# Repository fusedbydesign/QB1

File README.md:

# QB1

QB1 is a rapid prototyping system for ESP32 devices. The system was designed for ESPHome sensors, but it could potentially be used for other applications.

## Features

* Rapid prototyping for testing sensors and automation in the intended environment.
* Modular design allows each device to be built with the appropriate sensors, power interface, and mounting solutions. The five cube faces can each be used for a different purpose. 
* The QB1 specification allows multiple sensors to exist on the same device without conflict.
* Easy to make. 
  * The enclosure can be produced using a low cost 3D printer. 
  * The main board can be assembled quickly with basic soldering skills.
  * Many common sensor can be integrated by printing a custom face plate and connecting the sensor to the main board with Dupont wire. 
* Once constructed, the device can be modified without soldering, enabling rapid modification of devices. 

## Example Projects

<table>
  <tr>
    <td>
      <br>
      Washing machine monitor using SW-420 vibration sensor to detect when the machine is running and V53L0X distance sensor to tell when lid has been opened. The device is mounted to the washing machine using a custom mounting plate and velcro tape, and it is used to send a notification when wet clothes have been left in the wachine machine. 
    </td>
    <td>
      <br>
      Plug-in temperature and humidity monitor using SHT40. The device plugs in to the wall using an off-the-shelf USB wall plug that is inside the QB1 enclosure and held in place using a custom face plate. 
    </td>
  </tr>

  <tr>
    <td>
      <br>
      A wall-mounted human presence sensor that combines an AM312 PIR motion sensor and a wired magnetic reed door sensor. The device is used turn on/off lights in the area based on human presence. 
    </td>
    <td>
      <br>
      A ceiling-mounted device that combines human presence detection using an AM312 PIR motion sensor, car presence detection using an HC-SR04 distance sensor, and garage door control/status using a <a href="https://github.com/PaulWieland/ratgdo">ratgdo-compatible</a> peripheral board. 
    </td>
  </tr>
</table>

## Building

The core QB1 components can be built with basic tools and skills. 

> [!WARNING]
> This is an open source project and a constant work in progress, not a finished product. Production files and PCBWay projects are provided only for convenience. Boards ordered using these files/projects may have flaws due to issues in the design or assembly. The maintainers of this project are not responsible for loss or damages due to these flaws. Please submit any issues you find using the issue tracker for this project.  

### Tools Required

* A [soldering iron](https://amzn.to/4105tMp) and related supplies. The QB1 main board contains only through hole components, so only basic soldering skills are required. Some peripheral boards require surface mount components and more advanced soldering skills. 
* A basic 3D printer to print the QB1 enclosure and face plates. Using a print-on-demand service (or a friend with a printer) can help get you started, but having your own printer makes it much easier to print new faceplates to modify the device in the future. The [Bambu Lab A1 Mini](https://bambulab.com/en/a1-mini) (without AMS) is inexpensive and well-suited to printing smaller items like the QB1 enclosure. 
* A small Phillips screwdriver (or driver matching the head of the screws, if not Phillips). The shaft must be smaller than 5.5 mm in diameter in order to fit in the holes in the bottom of the enclosure. 
* A small tube of super glue to build some of the enclosure parts. 
* (Optional) A [hot glue gun](https://amzn.to/40Knkqm). Many sensors that operate at 3.3v can be connected directly to the main board using Dupont wire. It's best to glue these connectors in place so they don't fall off in operation. The hot glue can easily be removed later. 

### Components Required

All components other than custom circuit boards and 3D-printed enclosure parts can be purchased in small quantities from Amazon or AliExpress.

* A QB1 main board. You can order a small batch of 5 main boards using this [PCBWay project](https://www.pcbway.com/project/shareproject/QB1_Main_Board_for_ESP32_Development_Kit_a3892956.html). You can also use the zipped Gerber files provided in a QB1 release to order the board from another supplier. 
* A [30-pin ESP32 development board](https://amzn.to/4lGmVin) with USB-C connector. You can choose a device with the right storage and other features for your application.
* (7) [Female 15-pin, single row board header with 2.54 mm pin spacing](https://amzn.to/4suHbWA). You will need two for the ESP32 dev kit socket and up to 5 for the remaining QB4 faces.
* [Screws](https://amzn.to/47RIYwE): M3, self-tapping, coarse threaded with pan/button head. The head must be between 3.5mm and 5.5mm in diameter.
  * (8) To secure the main board and close the case, use screws that are 8mm long (not counting the head), but screws up to 16 mm in length will also work.
  * (4, Optional) To make the top plate removable and functional, use screws that are exactly 8mm long (not counting the head). In most cases, the top plate is not used for sensors or other peripherals, because the four side plates are sufficient. In this case, it can be glued in place, and these screws are unnecessary.
* [Printed enclosure parts](https://makerworld.com/en/collections/23142249-qb1): A top, a bottom, face plates for mounting and peripherals, and blank plates to cover any remaining faces. 
* (Optional) Any additional components required for peripherals. See peripheral doc for mor information. Some generally useful items to have on hand are:
  * [Dupont wire](https://amzn.to/4slY8CT) with male connector on one end and female connector on the other. The wire should be between 10 and 20cm in length. This wire is useful for hooking up small sensors that do not require a QB1 peripheral board. 
  * [Small prototyping boards](https://amzn.to/4sSRvYk) (e.g 40 mm by 60 mm) can be used to develop peripheral boards.  

### Assembling the Boards

Follow the instructions provided to assemble the QB1 [main board](/mainboards/ESP32DK) and any peripheral boards.

### Assembling the QB1

* Insert the ESP32 development board into the pair of 15-pin sockets on the bottom of the QB1 main board. Use the labels on the PCB silk screen to orient the ESP32 board correctly.  
* Place the main board on the tall screw hole supports inside the enclosure bottom. Ensure that the board is oriented correctly so that the ESP32 dev board screw holes rest on the lower supports and the USB-C connector faces the opening on the bottom plate. Screw the main board in place with 4 M3 screws.
* Place the USB-C port cover in the enclosure bottom and glue it in place with super glue. 
* Attach peripherals
  * For peripherals that are attached by wires, plug the connector into the appropriate place in the main board. Secure the connectors in place using hot glue, and attach the peripheral to its custom face plate.  
  * Attach peripheral boards to their custom plates. These boards typically have male header that connects to the main board and is held in place by the enclosure. This connection will be made when the face plates are inserted in a later step.
* Place the QB1 enclosure top upside down on a flat surface.
* Insert a face plate into the QB1 top face. The plate will be held lightly in place by friction against the screw supports. To hold this plate more firmly, place two top plate holders over the plate and screw them in place. 
* Place face plates into the four slots at the top of the enclosure. 
* Place the QB1 enclosure bottom upside down onto the top. To ensure that the peripheral boards are attached correctly to the main board connector: lift each perhipheral board slightly to make the connection, then lower the enclosure bottom after all connections are made. It may be necessary to wiggle the legs of the enclosure top to ensure that they are seated correctly. 
* Screw the bottom to the top using 4 M3 screws. 

## FAQ

* **When would I use this?** QB1 is useful in a few circumstances: 
  * When you want to quickly prototype a device to test its behavior in the intended environment. 
  * When you need multiple sensors in a single device.
  * When you need to deploy sensors in a basement/garage or other utility area where appearance/size is less important.
* **When wouldn't I use this?** There are some limitations:
  * QB1 is nearly 80 mm long on each side. For many applications, a custom board and enclosure would be smaller. 
* **How do I use this for home sensing and automation?** See the [ESPHome site](https://esphome.io) for more information. A typical solution is to set up a [Home Assistant](https://www.home-assistant.io) hub that takes information from QB1 devices (and other sensors). 
* **Does the QB1 look good?** Looks are subjective, but yes. 
* **What sensors are supported?** Any sensor that operates at 3.3v and has a fairly simple interface (a few IO pins, I2C, SPI, etc.) can be wired directly to the appropriate pins on the QB1 main board. Then all that is needed is a face plate that holds the sensor in place. Sensors/components with more complicated interfaces can be integrated by developing a peripheral board with additional interface components. 
* **How do I add an external connector?** The best ways to achieve this are:
  * Locate a panel-mount connector and attach it to the main board using wires.
  * Make a simple peripheral board with connectors soldered to it. A male JST-XH connector soldered to a peripheral board will sit approximately flush with the face plate. 
* **How do I configure ESPHome?** Locate ESPHome documentation for the sensor you would like to configure. Look at the main board documentation or silk screen markings on the main board to determine which pins are attached to each connector position. 
* **What happens if I plug in multiple peripherals? How do I keep them from conflicting?** The QB1 spec assigns pins to each peripheral position. Some pins are shared, such as pins intended for the I2C and SPI buses. Each peripheral position also has four pins that are dedicated to that position (with the exception of EB2 and EB5, that have the same set of "dedicated" pins). Where possible, a peripheral should use dedicated pins or buses in order to avoid conflict.
* **The screws are too tight/loose. What is wrong?** To keep the part count low, the design does not use screw inserts, and instead uses self-tapping screws that screw into 3D-printed holes. Due to variation in printers and settings, these holes may be slightly too large/small. To fix it:
  * If the hole is too tight, carefully drill it out. Forcing the screw in without drilling may cause the plastic to crack.
  * If the hole is too loose, add a small amount of hot glue, allow the glue to cool, then screw in the screw. Hot glue can also be used to repair screw holes that are cracked or worn out. 
* **What options should I select when ordering boards from PCBWay?** Unless you have a compelling reason to change the options, you can use the default settings when ordering boards. 
* **How can I get a QB4 if I don't have a 3D printer or soldering iron?** There are a few options:
  * Order assembled boards and printed enclosure parts from an electronics fab and print-on-demand service, respectively.
  * Join a local maker space that has 3D printers and electronics assembly tools. 
  * Find someone near you with a 3D printer and buy enclosure parts from them. Many people who own a 3D printer would be thrilled to print something for you in exchange for a small amount of money to pay for their filament habit. 
  * Use this project as an excuse to buy what you need. Soldering supplies are inexpensive. Small/basic 3D printers are now cheap and reliable enough that they should be considered essential tools for any homeowner. 

## Support and Transparency

If you are fortunate enough to have a store near you that sells basic electronics components, please consider buying components from them instead of using the links on this site or ordering from internet retailers.

I (the developer of QB1) earn a commission from tools and components purchased though links on this site. As an Amazon Associate, I earn from qualifying purchases. I also earn a commission from circuit boards ordered from PCBWay. I chose the recommended tools/components by searching for products with the correct specs and features, but I haven't tried them all. Please review the product description, specs, reviews, etc. before ordering.

If you would like to directly support the development of QB1, you can donate using [Buy me a coffee](https://buymeacoffee.com/fusedbydesign).

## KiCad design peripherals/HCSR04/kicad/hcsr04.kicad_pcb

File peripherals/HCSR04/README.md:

# HC-SR04 Distance Sensor Peripheral Board for QB1

The HC-SR04 is a low-cost ultrasonic distance sensor with sub-centimeter precision and a maximum range of 4 meters. Unfortunately, it needs to operate at 5V for best performance, and its output must be converted to 3.3V in order to interface with the ESP32 without damaging it. This board provides a safe, reliable 5v/3.3V interface between the ESP32 and an HC-SR04. The board also provides a physical mounting surface for the HC-SR04, and a second level converter that can be used to connect another HC-SR04 that is mounted elsewhere. 

> [!TIP]
> There are other distance sensors that can interface more easily with the QB1 without level conversion. There are also HC-SR04P modules that can be powered using 3.3v, but the maximum range will be slightly reduced. Be prepared to test multiple distance sensors to find the ones that work best for your application.

## Printed Circuit Board

The easiest way to get the PCB is to order a batch using this [PCBWay project](https://www.pcbway.com/project/shareproject/QB1_peripheral_board_for_HC_SR04_distance_sensor_22c7cf84.html). Due to the options for mounting the sensor module, and the unusual way the module is mounted in some options, DIY assembly is highly recommended. Assembly only requires a few through hole components and some basic soldering skills. 

## Required components

| Count | Description |
|---|---|
| 1 | [HC-SR04 module](https://amzn.to/4rNMYFK)|
| 1 | 15 pin male header, 2.54mm pin spacing, angled |
| 2 | 100k Ohm resistor, through hole, axial |
| 2 | 51k Ohm resistor, through hole, axial |
| 4 | Single pin male header, straight |
| 1 | (Optional) 4-pin male header, 2.54mm spacing, angled | 

Component notes:
* For the angled header, you can use commonly-available [breakaway header](https://amzn.to/4sulC8Q) and break it to the correct size. Ensure the header has a short post (the straight part---approximately 3mm long) and a longer tail (the bent part---approximately 6mm long after the bend). The post of the header is soldered to the board and the connector sits 4-5mm off the board. These dimensions ensure a proper fit using the face plate for this connector. Other connectors may be used by modifying the face plate.
* Any [resistors](https://amzn.to/4bEVNeX) with 5% or smaller tolerance and at least 1/4 watt power capacity will work. You can modify the resistance to match the resistor values you have available, as long as the ratio remains approximately 1:2. For example, a 47k Ohm reistor can be used instead of 51k. Increasing the resistance (while maintaining a ratio of 1:2) is not recommended, but the values can be lowered to a minimum of 1k/2k, if desired. The value of 51k/100k was chosen to give acceptable performance in most environments while minimizing power draw. If the sensor will be used in an environment with a large amount of electromagnetic interference, then lower resistance values may give more reliable performance, at the expense of slightly more power draw.

## Assembly

The board supports two different orientations for the HC-SR04:
* Straight mount so that the HC-SR04 and board occupy a single cube face. This is the most common orientation.
* Edge mount so the board can be mounted in one of the side faces and the HC-SR04 points in the direction of the top face. This orientation allows the HC-SR04 to point in the direction of the top face, without the complications associated with mounting the board on the top face. 

Take note of the order in which the components must be placed and soldered---the HC-SR04 covers some of the other components, so it must be placed last. To assemble:

1. Place and solder the resistors as shown in the silk screen on the back of the board, and the 15-pin header on the front of the board.  
1. If the second interface will be used to connect a second HC-SR04 to the QB1, place and solder the 4-pin angled header.
1. Attach the HC-SR04 module and related components
  * For straight mount, start by placing and soldering the single pin headers on the front side of the board, as shown in the silk screen. These headers are not connected, and are only used for structural support. Next, bend the pins on the HC-SR04 module to make them straight, then place the HC-SR04 module, ensuring the pins on the single headers extend through the mounting holes at the corners of the module. With the module seated flush against the base of the headers, solder the module pins to the board. Finally, cut the excess pin length from the module pins and single pin headers using wire cutters. 
  * For edge mount, place and solder the HC-SR04 module in the U2 position on the back of the board, with the sensor pointing away from the board. Cut the excess pin length from the HC-SR04 connector.
  
The peripheral board mounts to the main board in the inside position, in order to accommodate the depth of the sensor module. 

## Enclosure 

Print or otherwise obtain the [face plate](https://makerworld.com/en/models/2567128-qb1-face-plate-for-hc-sr04-peripheral-board) to incorporate this peripheral board into a QB1. To complete the enclosure, you will also need other pieces from [this collection](https://makerworld.com/en/collections/23142249-qb1).

## Operation

For the HC-SR04 mounted to the peripheral board, the trigger pin is connected to TRIG1, and and the echo pin is connected to ECHO1. For the optional external HC-SR04, these signals are TRIG2 and ECHO2. See the silk screen on the board for the connection between these signals and QB1 peripheral pins. 

See the [ESPHome](https://esphome.io/components/sensor/ultrasonic/) page on ultrasonic distance sensors for more information about the HC-SR04 and how to use it with ESPHome.

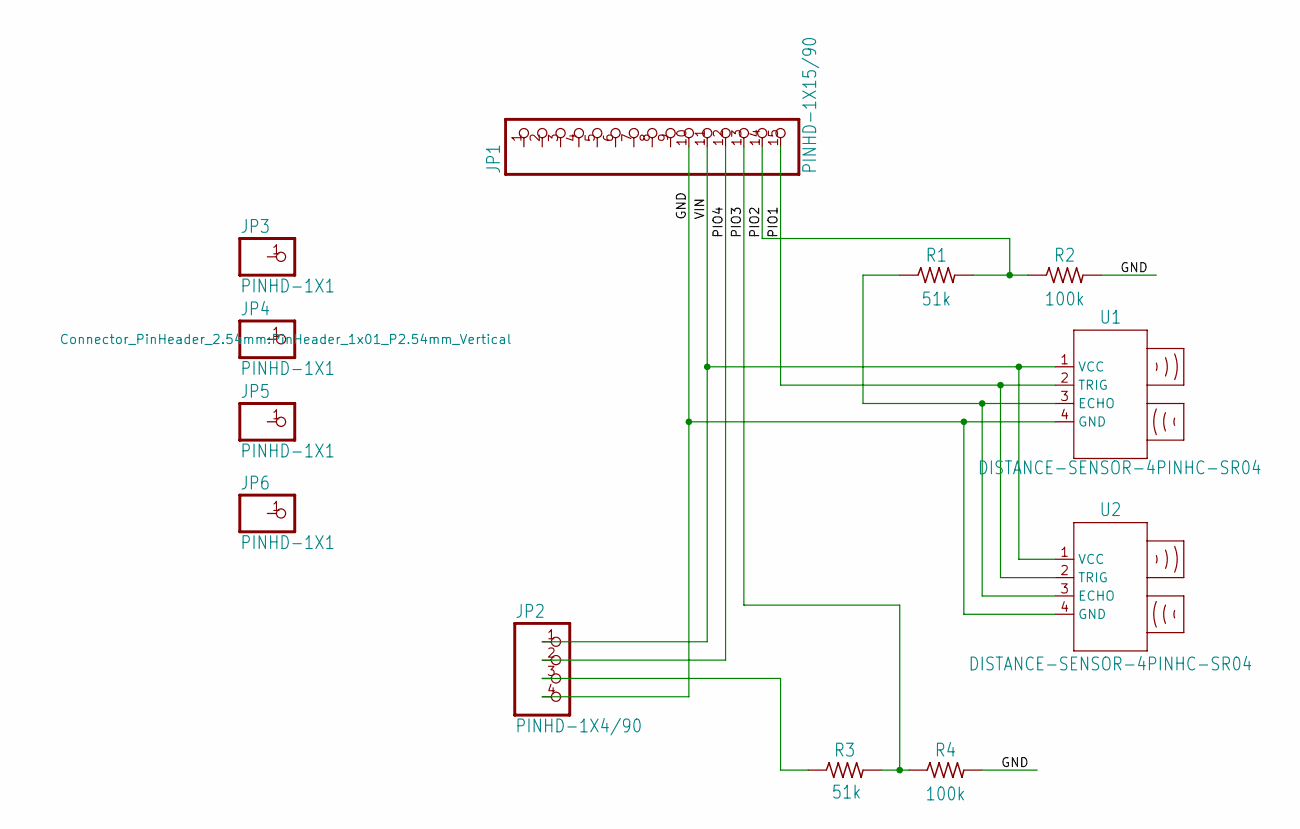
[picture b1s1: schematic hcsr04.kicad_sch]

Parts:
JP1: PINHD-1X15/90; PinHeader_1x15_P2.54mm_Horizontal
JP2: PINHD-1X4/90; PinHeader_1x04_P2.54mm_Horizontal
JP3, JP4, JP5, JP6: PINHD-1X1; PinHeader_1x01_P2.54mm_Vertical
R1, R3: 51k; R_Axial_DIN0207_L6.3mm_D2.5mm_P7.62mm_Horizontal
R2, R4: 100k; R_Axial_DIN0207_L6.3mm_D2.5mm_P7.62mm_Horizontal
U1, U2: DISTANCE-SENSOR-4PINHC-SR04; HC-SR04

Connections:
/GND: JP1.10, JP2.4, R2.2, R4.2, U1.4 (GND), U2.4 (GND)
/PIO1: JP1.14, JP1.15, R1.2, R2.1, U1.2 (TRIG), U2.2 (TRIG)
/PIO3: JP1.13, R3.2, R4.1
/PIO4: JP1.12, JP2.2
/VIN: JP1.11, JP2.1, U1.1 (VCC), U2.1 (VCC)
unnamed: JP2.3, R3.1
unnamed: R1.1, U1.3 (ECHO), U2.3 (ECHO)

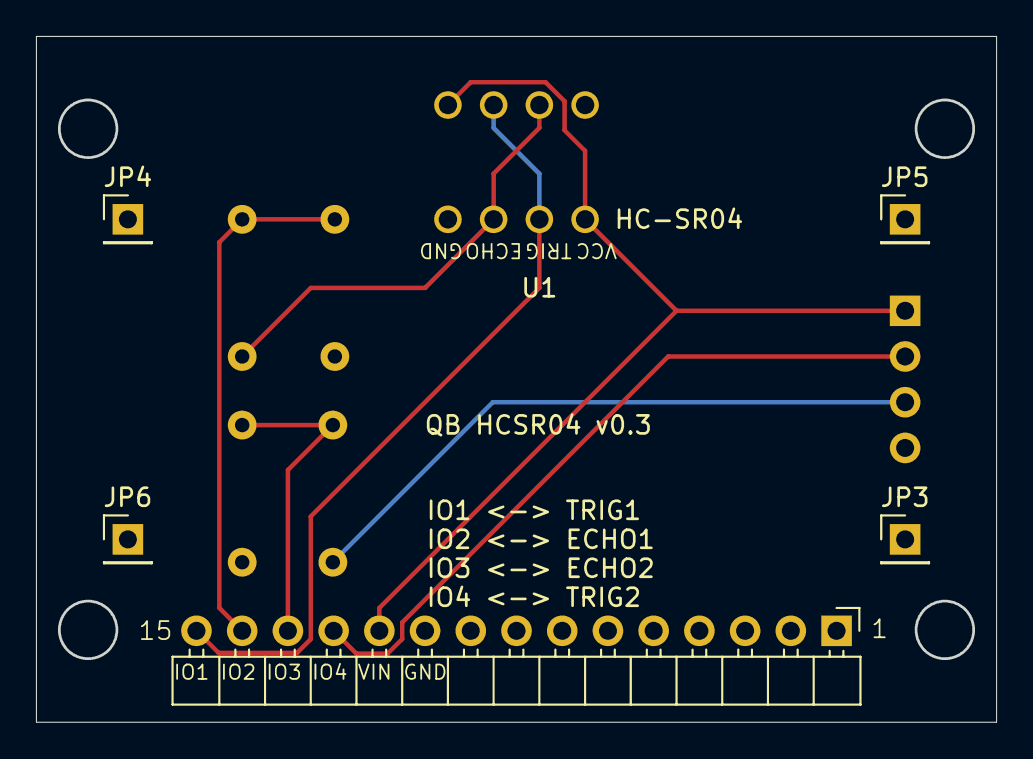
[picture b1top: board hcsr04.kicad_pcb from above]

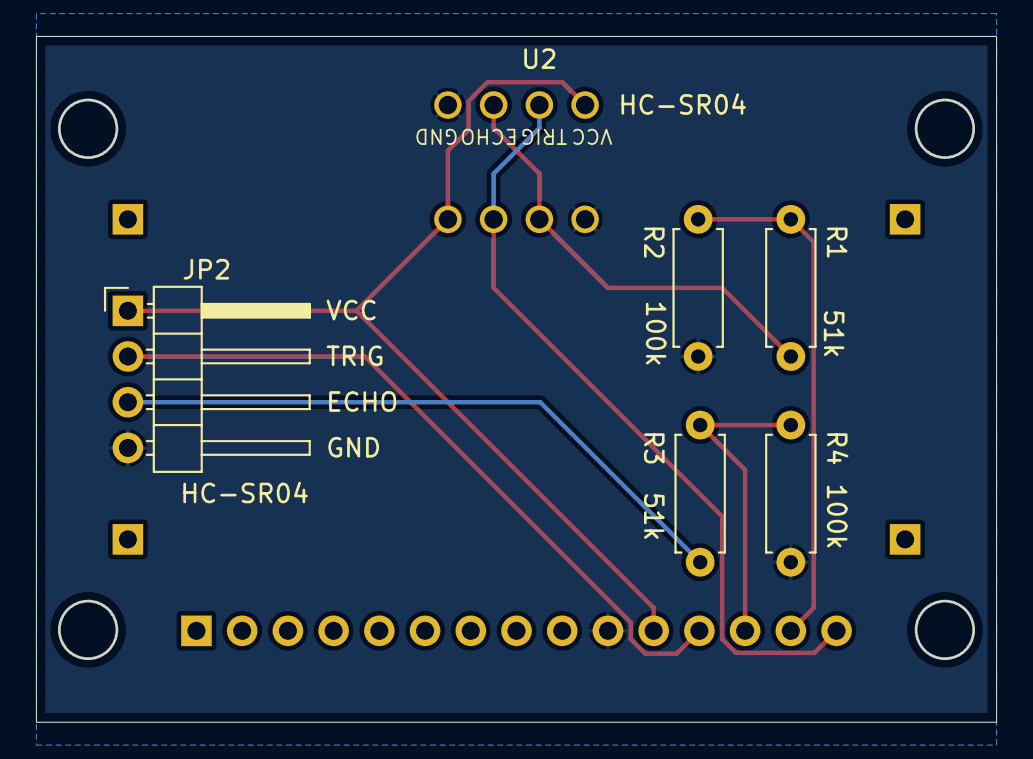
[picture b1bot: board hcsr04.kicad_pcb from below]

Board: 2 copper layers, 53.2 x 38.0 mm, 12 parts (6 on the bottom side), 7 nets.

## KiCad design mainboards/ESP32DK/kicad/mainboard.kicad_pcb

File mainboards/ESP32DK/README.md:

# QB1 ESP32 Dev Kit Main Board

The ESP32 Dev Kit Main Board adapts a 30-pin ESP32 dev dev to the QB1. This is the main component required to build a QB1 using an ESP32 dev kit. 

## Printed Circuit Board

The easiest way to get the PCB is to order a batch using this [PCBWay project](https://www.pcbway.com/project/shareproject/QB1_Main_Board_for_ESP32_Development_Kit_a3892956.html). You can also get an assembled board, but the board has been designed to make DIY component sourcing and assembly very easy.  

## Required components

| Count | Description |
|---|---|
| 7 | Female header with 2.54mm spacing, 15-pin |

## Assembly

* Solder 15-pin female header connectors to the locations on indicated for the ESP32 dev kit, and also to any peripheral locations that will be used. Note that connectors for the dev kit go on the bottom of the board, while the connectors for the peripherals go on the top. Use the PCB silk screen as a guide, and only place connectors where the holes are surrounded by a border on the silk screen.  
* Solder additional connectors for power and reset connections, as needed. In many cases, these connectors are unnecessary. These connectors are only necessary if you want to add a poer source or reset switch without using one of the peripheral spots.  

## Enclosure

Print or otherwise obtain the [enclosure bottom](https://makerworld.com/en/models/2543156-qb1-bottom-for-esp32-dev-kit-main-board) to incorporate this main board into a QB1. To complete the enclosure, you will also need a top piece and window pieces/blanks. All QB1 enclosure pieces are available in [this collection](https://makerworld.com/en/collections/23142249-qb1).

## Operation

### Power

Power can be supplied to this board through the USB connector on the development kit, or by a power supply peripheral. When powering by USB, the USB power supply must provide at least 2A for the full power configuration, or 1A for low power configuration. See the [QB1 specification](/spec) for more information about power configurations. 

### Connectors

This main board has four peripheral connectors labeled EB1-5. EB5 is in the center of the board, and it can be used to wire up a peripheral mounted to the top plate. All connectors are wired to different host pins for PIO, except for EB2 and EB5, which share the same host pins for PIO. So peripherals that use (the same) PIO pins cannot operate in EB2 and EB5 at the same time. 

### Pin Mapping

| Pin # | Connector | Host |
|---|---|---|
| 1 | AUX | Not Connected |
| 2 | S | D25 |
| 3 | MOSI | D23 |
| 4 | MISO | D19|
| 5 | CLK | D18 |
| 6 | EN | EN |
| 7 | SCL | D22 |
| 8 | SDA | D21 |
| 9 | 3V3 | 3V3 |
| 10 | GND | GND |
| 11 | VIN | VIN |

| Pin # | Connector | Host EB1 | Host EB2 | Host EB3 | Host EB4 | Host EB5 |
|---|---|---|---|---|---|---|
| 12 | PIO4 | D12 | D4 | D2 | D15 | D4 |
| 13 | PIO3 | D36 | D39 | D34 | D35 | D39 |
| 14 | PIO2 | D27 | D13 | D14 | D33 | D13 |
| 15 | PIO1 | D16 | D17 | D26 | D32 | D17 |

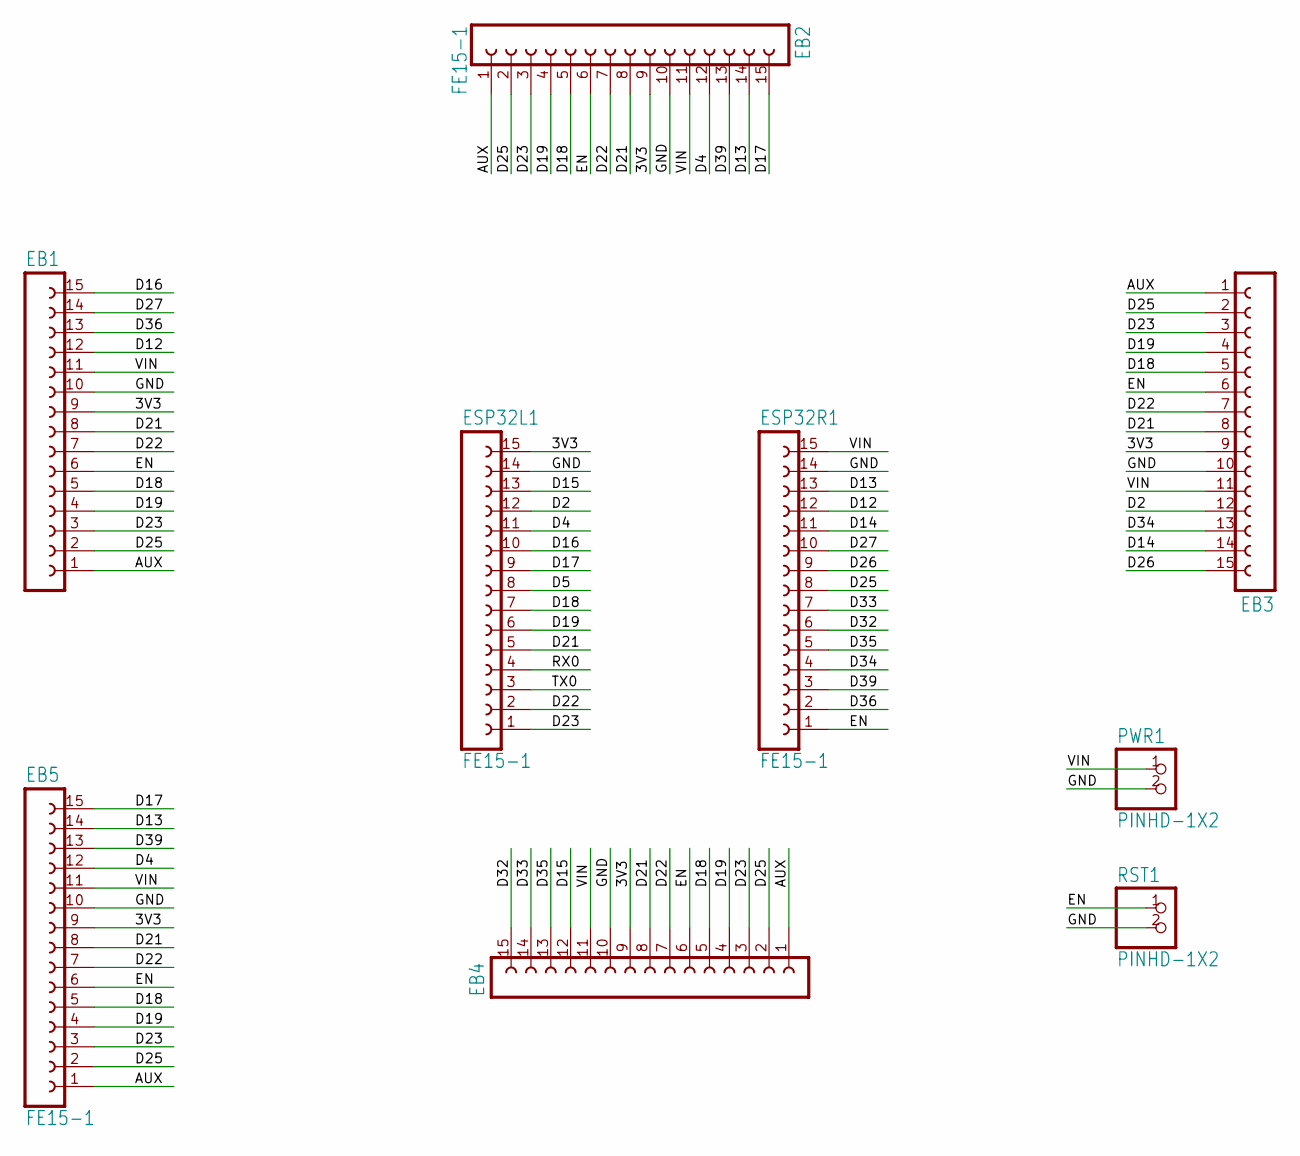
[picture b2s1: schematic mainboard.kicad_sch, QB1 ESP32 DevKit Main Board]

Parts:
EB1, EB3, EB4: PinSocket_1x15_P2.54mm_Vertical
EB2, EB5: FE15-1; PinSocket_1x15_P2.54mm_Vertical
ESP32L1, ESP32R1: FE15-1; PinSocket_1x15_P2.54mm_Vertical
PWR1: PINHD-1X2; PinHeader_1x02_P2.54mm_Vertical
RST1: PINHD-1X2; PinHeader_1x02_P2.54mm_Vertical

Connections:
/3V3: EB1.9, EB2.9, EB3.9, EB4.9, EB5.9, ESP32L1.15
/AUX: EB1.1, EB2.1, EB3.1, EB4.1, EB5.1
/D2: EB3.12, ESP32L1.12
/D4: EB2.12, EB5.12, ESP32L1.11
/D5: ESP32L1.8
/D12: EB1.12, ESP32R1.12
/D13: EB2.14, EB5.14, ESP32R1.13
/D14: EB3.14, ESP32R1.11
/D15: EB4.12, ESP32L1.13
/D16: EB1.15, ESP32L1.10
/D17: EB2.15, EB5.15, ESP32L1.9
/D18: EB1.5, EB2.5, EB3.5, EB4.5, EB5.5, ESP32L1.7
/D19: EB1.4, EB2.4, EB3.4, EB4.4, EB5.4, ESP32L1.6
/D21: EB1.8, EB2.8, EB3.8, EB4.8, EB5.8, ESP32L1.5
/D22: EB1.7, EB2.7, EB3.7, EB4.7, EB5.7, ESP32L1.2
/D23: EB1.3, EB2.3, EB3.3, EB4.3, EB5.3, ESP32L1.1
/D25: EB1.2, EB2.2, EB3.2, EB4.2, EB5.2, ESP32R1.8
/D26: EB3.15, ESP32R1.9
/D27: EB1.14, ESP32R1.10
/D32: EB4.15, ESP32R1.6
/D33: EB4.14, ESP32R1.7
/D34: EB3.13, ESP32R1.4
/D35: EB4.13, ESP32R1.5
/D36: EB1.13, ESP32R1.2
/D39: EB2.13, EB5.13, ESP32R1.3
/EN: EB1.6, EB2.6, EB3.6, EB4.6, EB5.6, ESP32R1.1, RST1.1
/GND: EB1.10, EB2.10, EB3.10, EB4.10, EB5.10, ESP32L1.14, ESP32R1.14, PWR1.2, RST1.2
/RX0: ESP32L1.4
/TX0: ESP32L1.3
/VIN: EB1.11, EB2.11, EB3.11, EB4.11, EB5.11, ESP32R1.15, PWR1.1

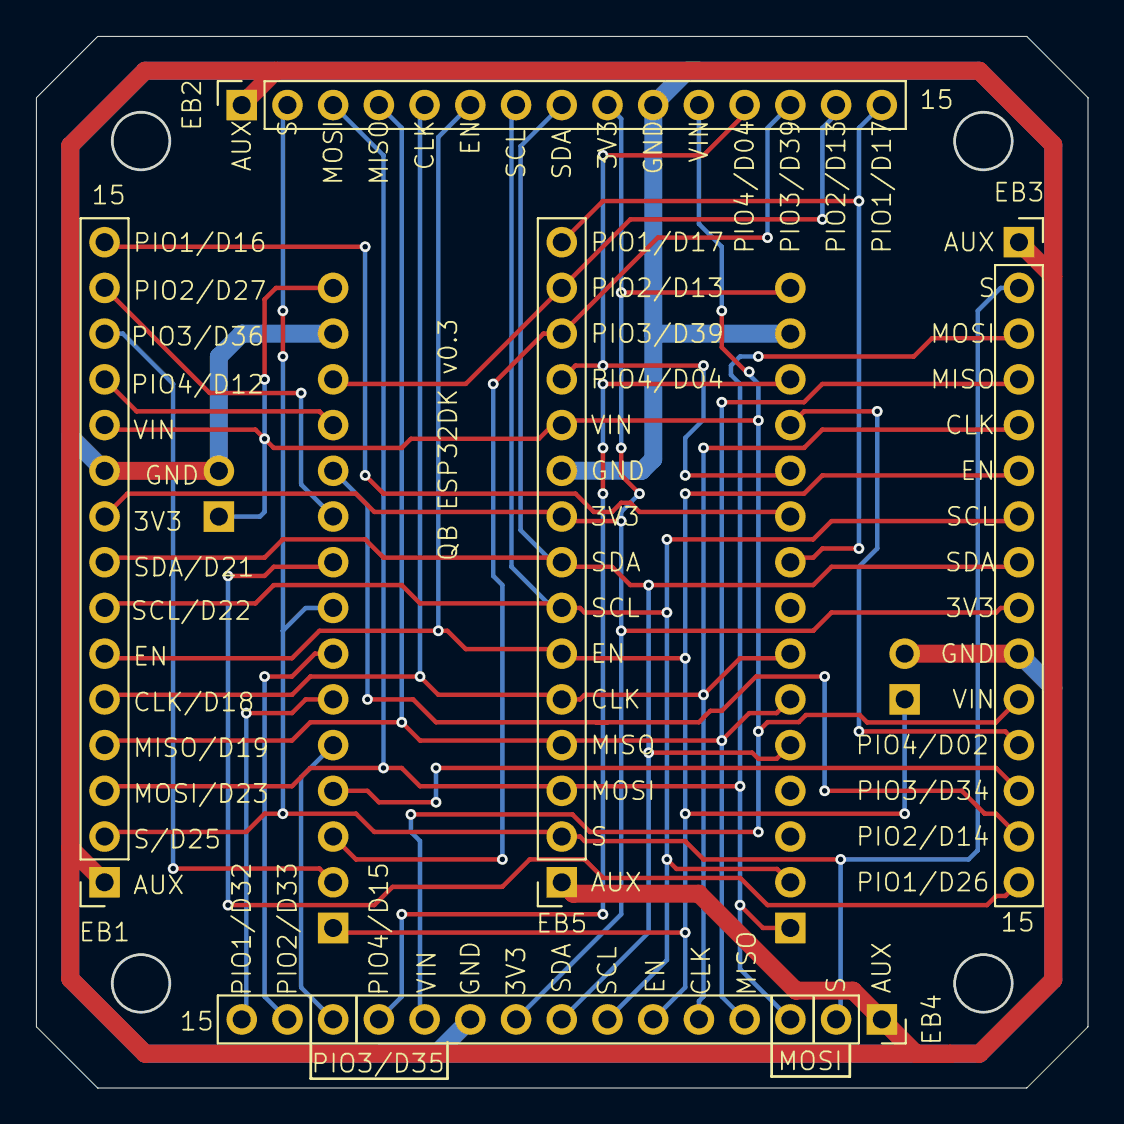
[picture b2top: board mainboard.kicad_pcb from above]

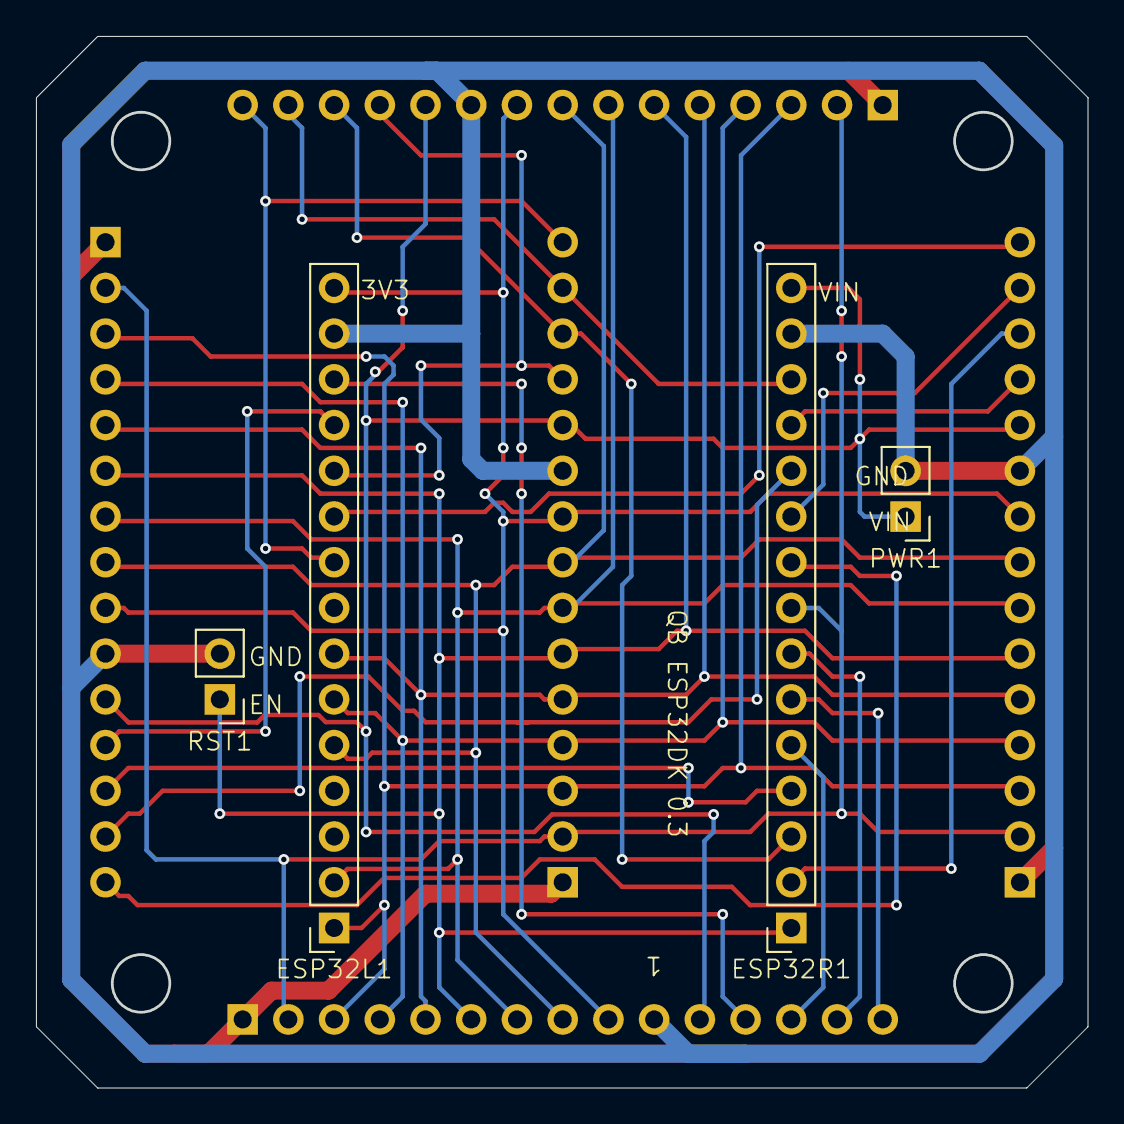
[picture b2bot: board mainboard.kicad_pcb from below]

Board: 2 copper layers, 58.3 x 58.3 mm, 9 parts (4 on the bottom side), 27 nets.

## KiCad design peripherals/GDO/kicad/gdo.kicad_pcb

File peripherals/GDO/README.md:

# Garage Door Opener Board for QB1

The Garage Door Opener (GDO) board allows the QB1 to directly interface with Chamberlain/Liftmaster garage door openers that cannot be controlled with dry contacts. 

This peripheral is inspired by the [ratgdo](https://ratcloud.llc), and it is designed to be compatible with [ratgdo firmware](https://paulwieland.github.io/ratgdo/flash.html). If you simply want to connect your garage door opener to your home automation system, please consider buying a ratgdo board. Some models even include additional components that make it easy to solve additional garage sensing/control problems (car presense, parking distance) with the ratgdo. The QB1 GDO peripheral is designed for circumstances in which a ratgdo needs to be combined with other sensors/peripherals. It can also be used to address unusual power or mounting circumstances. 

The schematic and technical information used to develop this project are due to the [rat-ratgdo project](https://github.com/Kaldek/rat-ratgdo). 

## Printed Circuit Board

The easiest way to get the PCB is to order a batch using this [PCBWay project](https://www.pcbway.com/project/shareproject/QB1_garage_door_opener_peripheral_board_5e12e1d1.html). This project can also be used to purchase assembled boards. 

> [!CAUTION]
>Assembling this peripheral is somewhat challenging because it is necessary to obtain and solder surface mount components. The soldering is possible with a normal soldering iron with a fine tip. Search on YouTube for instructional videos. You will probably also want additional tools such as a vise, a desk-mounted magnifying glass, and tweezers. 

## Required components

| Count | Description |
|---|---|
| 1 | 3-pin male JST-XH PCB connector, through hole, straight |
| 1 | 2N7002 transistor, surface mount, SOT-23 |
| 2 | AO3400A transistor, surface mount, SOT-23 |
| 3 | 10k Ohm resistor, surface mount, 0805, 1%, 1/4W |
| 1 | 15-pin male header with 2.54mm spacing, angled, 6mm mating length, 3mm tail length |
| 1 | (Optional) 2-pin male header with 2.54mm spacing, straight, 6mm mating length, 3mm tail length| 
| 1 | (Optional) 2-pin jumper with 2.54mm spacing | 

It is also necessary to obtain a wire to connect the peripheral to the terminals on the garage door opener. The best way to do this is to crimp a female JST-XH connector onto one end of a ribbon or set of wires, and leave the other end bare so the wires can be attached to the terminals on the garage door opener. See the board silk screen to determine the proper connections. 

## Assembly

1. Place and solder the the surface mount components on the front side of the board. 
1. Place and solder the 3-pin JST connector, after selecting the appropriate location. 
  * To allow the peripheral to be installed in a side face of the QB1 (the most common mounting), the connector should placed in the location marked J4 on the back side of the board.
  * The connector can be soldered in other positions, or even left off the board, to support less common methods of mounting the board and connecting to the garage door opener. 
1. Place and solder the 15-pin angled header on the front side of the board. The board may not have silk screen markings to indicate the correct side of the board for the header. It should be placed on the same side as the surface mount components.  
1. (Optional) place and solder the 2-pin male jumper at position J2 on the front of the board. 

The 2-pin male header is used to optionally connect the CTRL signal from the garage door opener to the QB1 AUX line. This optional connection can be made by placing a jumper on the header. The connection allows other peripherals to use the CTRL signal (e.g. to make a power supply).

The peripheral board mounts to the main board in the outside position, which allows the JST-XH connector to sit roughly flush with the window. 

## Enclosure

A [face plate](https://makerworld.com/en/models/2606454-qb1-plate-for-garage-door-opener-peripheral-board) is available for this peripheral. Attach the peripheral board to the face plate using 4 M3x8mm self-tapping screws. 

## Operation

The easiest way to use the GDO peripheral is to start with the appropriate [ratgdo firmware](https://paulwieland.github.io/ratgdo/flash.html) and modify the configuration so that the firmware communicates with the GDO using the correct pins. See the silk screen on the peripheral board for the connection between the GDO and QB1 connector. Also see the [main board README](/mainboards/ESP32DK) for the mapping between QB1 connector pins and ESP32 pins.  

The ESPHome ratgdo firmware is available on github, and there is also a convenient [downloader](https://ratgdo.github.io/esphome-ratgdo/). Any firmware that uses the correct host SoC family (e.g. ESP32 for the QB1 ESP32 dev kit main board) should work after the pins are correctly configured. The ESPHome configuration can then be modified to enable additional peripherals on the device.

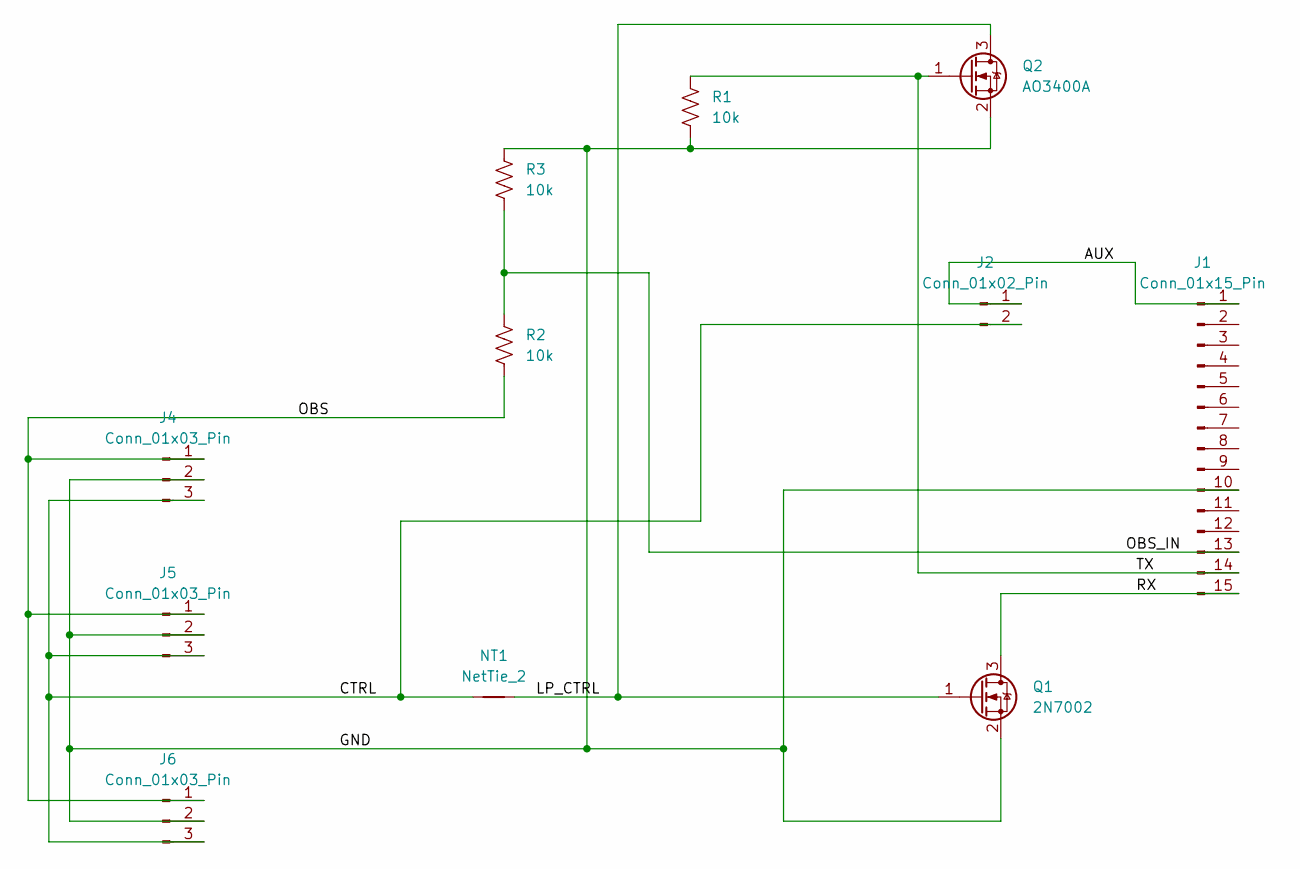
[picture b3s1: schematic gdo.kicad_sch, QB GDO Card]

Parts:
J1: Conn_01x15_Pin; PinHeader_1x15_P2.54mm_Horizontal
J2: Conn_01x02_Pin; PinHeader_1x02_P2.54mm_Vertical
J4, J5, J6: Conn_01x03_Pin; PinHeader_1x03_P2.54mm_Vertical
NT1: NetTie_2; NetTie-2_THT_Pad1.0mm
Q1: 2N7002; SOT-23
Q2: AO3400A; SOT-23
R1, R2, R3: 10k; R_0805_2012Metric_Pad1.20x1.40mm_HandSolder

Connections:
/AUX: J1.1, J2.1
/CTRL: J2.2, J4.3, J5.3, J6.3, NT1.1
/GND: J1.10, J4.2, J5.2, J6.2, Q1.2 (S), Q2.2 (S), R1.2, R3.1
/LP_CTRL: NT1.2, Q1.1 (G), Q2.3 (D)
/OBS: J4.1, J5.1, J6.1, R2.2
/OBS_IN: J1.13, R2.1, R3.2
/RX: J1.15, Q1.3 (D)
/TX: J1.14, Q2.1 (G), R1.1

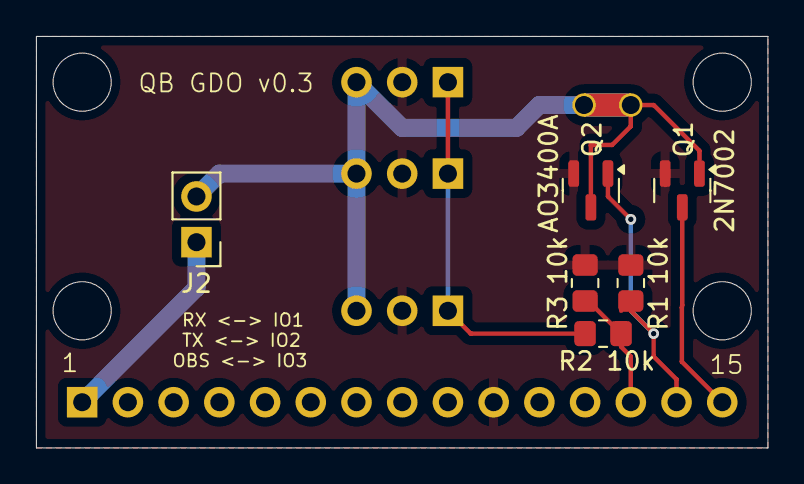
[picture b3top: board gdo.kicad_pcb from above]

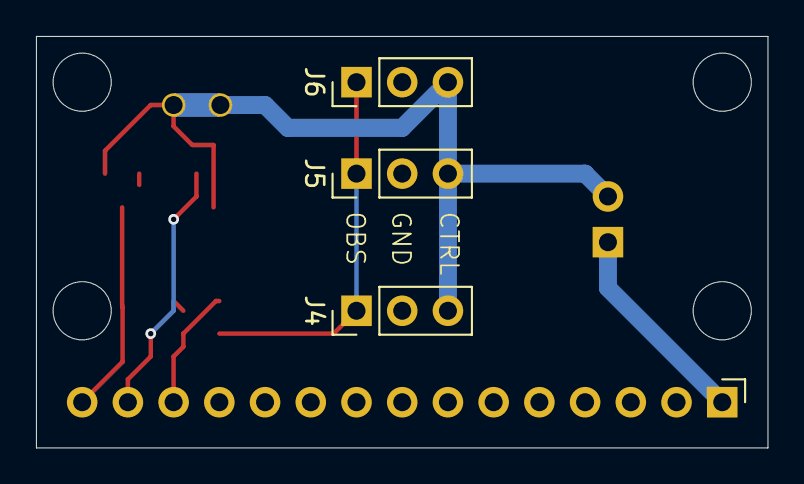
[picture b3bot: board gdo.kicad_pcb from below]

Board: 2 copper layers, 40.6 x 22.9 mm, 11 parts (5 on the bottom side), 8 nets.

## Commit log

2026-03-17 Initial commit with top level and board files.
2026-03-17 Adding README for HC-SR04
2026-03-17 Readme tweaks
2026-03-18 Adding spec and GDO README files.
2026-03-19 README tweaks.
2026-03-19 Adding links to enclosure pieces.
2026-03-19 Adding external links to top-level README.
2026-03-19 Fixing a link.
2026-03-20 Adding BOM for main board.
2026-03-24 Completing HC-SR04 peripheral, and other minor changes.
2026-03-25 * Loosening up the spec so that only connector-to-plate distance is specified. Peripherals are free to choose connectors and board thickness, and this may cause the board-to-plate distance to vary. *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
2026-03-25 Adding a FAQ entry and tweaking some wording in the spec.
2026-04-02 Adding GDO peripheral BOM, PCBWay project, and enclosure face plate.
